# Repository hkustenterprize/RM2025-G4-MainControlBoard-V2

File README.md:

<div align='center'>
    <h1>RM2025 G4主控板V2</h1>
</div>

<div align='center'>
    <h2>RM2024香港科技大学ENTERPRIZE</h2>
</div>

**开源论坛链接：**

**欢迎加入开源交流QQ群：581184202**

## 文件内容

核心板：[点击在线预览](https://kicanvas.org/?github=https%3A%2F%2Fgithub.com%2Fhkustenterprize%2FRM2025-G4-MainControlBoard-V2%2Ftree%2Fmain%2FRM2025_G473_MCB)

扩展板：[点击在线预览](https://kicanvas.org/?github=https%3A%2F%2Fgithub.com%2Fhkustenterprize%2FRM2025-G4-MainControlBoard-V2%2Ftree%2Fmain%2FRM2025_G473_MCB_StdExtend)

~~~
RM2025-G4-MainControlBoard-V2
├── image
├── RM2025_G473_MCB             > 核心板工程文件
├── RM2024_G473_MCB_StdExtend   > 标准扩展板工程文件
├── LICENSE
└── README.md
~~~

开源工程文件设计软件为 **KiCAD 8.0**，可以导入立创EDA

每个工程文件文件夹中的内容:

~~~
xxx
├── ibom             > 焊接工具，由 "Interactive HTML BOM" 插件生成
├── production      > 生产文件，由 "Fabrication Toolkit" 插件生成，将其中的zip文件拖入JLC下单助手即可
├── xxx.kicad_pcb   > PCB
├── xxx.kicad_pro   > 主工程，通过双击这个启动KiCAD
└── xxx.kicad_sch   > 原理图
~~~

## 重要参数

主控板分为核心板（下板）和扩展板（上板），两板之间使用80pin BTB接口连接，尺寸上保持为与C板一致的 60x40mm；核心板包含所有核心芯片，扩展板用于引出接口或进行其他功能的扩展。

- MCU: STM32G473VET6
- IMU: ICM-42688P
- TTL: CH343P *2 
- FDCAN *3
- RS485 (硬件流控) *1
- FLASH: W25N01GVZEIG

## 主要变动

较比上代开源（[RM2024 G4主控板开源](https://github.com/hkustenterprize/RM2024-MainControlBoard)），2025赛季的G4主控板根据需求做出了一些变动和优化，主要变化如下：

- 核心板重新 layout，将 QSPI FLASH 的走线进行了等长
- 移除磁力计，移除 CH343P 的流控引脚连接
- 在核心板上增加两个 GPIO 接口
- 将核心板的 MCU 供电由 Buck 改为 LDO
- 扩展板重新 layout，增加了专用于舵轮分电板的 7pin 接口
- 扩展板增加四个 WS2812 LED用于指示状态，将蜂鸣器移至核心板上

## 电源网络

## 外设引脚分配

| <u>CAN</u> (SIT1042T/3) | CAN_TX | CAN_RX |
| ---- | ---- | ---- |
| **CAN1**   | PD1   | PD0   |
| **CAN2**   | PB6   | PB5  |
| **CAN3**   | PB4   | PB3   |

| <u>RS485</u> (SN75176AD) | TX <sup>1</sup> | RX <sup>1</sup> | DE <sup>2</sup>|
| ---- | ---- | ---- |---- |
| **RS485 (UART4)**   | PC10   | PC11  | PA15 |

1. 不使用RS485功能时 UART4 可作为 独立UART 使用。
2. 不使用RS485功能时 **DE引脚** 需要配置为 **高电平**，需要确保 **RS485接口** 没有连接。

| <u>TTL</u> (CH343P) | TX | RX |
| ---- | ---- | ---- |
| **TTL1 (UART2A)**   | PA2  | PA3  |
| **TTL2 (UART3A)**   | PD8  | PD9  |

- 两个TTL芯片均连有状态指示灯，在接口两侧。
- CH343P 接入USB线 (VBUS有供电) 后自动使能。

| <u>IMU</u> (ICM-42688P) | SCLK | MISO | MOSI | CS | DRDY |
| ---- | ---- | ---- | ---- | ---- | ---- |
| **IMU (SPI2)**   | PB13  | PB14  | PB15 | PB12 | PB10 |

- **IMU加热**开关由 **PA4** 引脚控制，可以使用 **TIM3_CH2** 或 **GPIO SET/RESET**。
- IMU朝向已在板背面标明

| <u>DR16/i10B</u> | RX <sup>1 2</sup> |
| ---- | ---- |
| **RX1 (UART1C)**   | PA10 |
| **RX2 (UART3C)**   | PB11 |

1. 两个引脚硬件上连接在一起，可使用任意一个引脚 (对应的串口) 读取接受机数据。
2. 使用一个引脚时，**另外一个引脚一定要悬空**。

| <u>FLASH</u> (W25N01GVZEIG) | CS | CLK | IO0 | IO1 | IO2 | IO3 |
| ---- | ---- | ---- | ---- | ---- | ---- | ---- |
| **FLASH (QSPI1)**   | PE11  | PE10  | PB1 | PE13 | PE14 | PA6 |

| <u>其他外设</u>  | Pin |
| ---- | ---- |
| **VIN 24V ADC**   | PA8  |
| **5V ADC**   | PA9  |
| **Buzzer**   | PE3  |
| **LED**   | PC13  |
| **Button**   | PC15  |

## 串口分配

|       | TX | RX | DE | 功能 |
| ---- | ---- | ---- | ---- | ---- |
| **UART1A**   | PC4  | PC5  |-      | 裁判系统/图传 |
| **UART1B**   | PE0  | PE1  |- | 通用串口  |
| **UART1C**   | -  | PA10  |-  | 接收机  |
| **UART2A**   | PA2  | PA3  |-  | MiniPC1 TTL |
| **UART2B**   | PD5  | PD6  |-  | 通用串口  |
| **UART3A**   | PD8  | PD9  |-  | MiniPC2 TTL |
| **UART3B**   | PB9  | PE15  |-  | 通用串口  |
| **UART3C**   | -  | PB11  |-  | 接收机  |
| **UART4**   | PC10  | PC11  | PA15 | RS485/通用串口<sup>1</sup>  |
| **UART5**   | PC12  | PD2  |-  | 裁判系统/图传  |

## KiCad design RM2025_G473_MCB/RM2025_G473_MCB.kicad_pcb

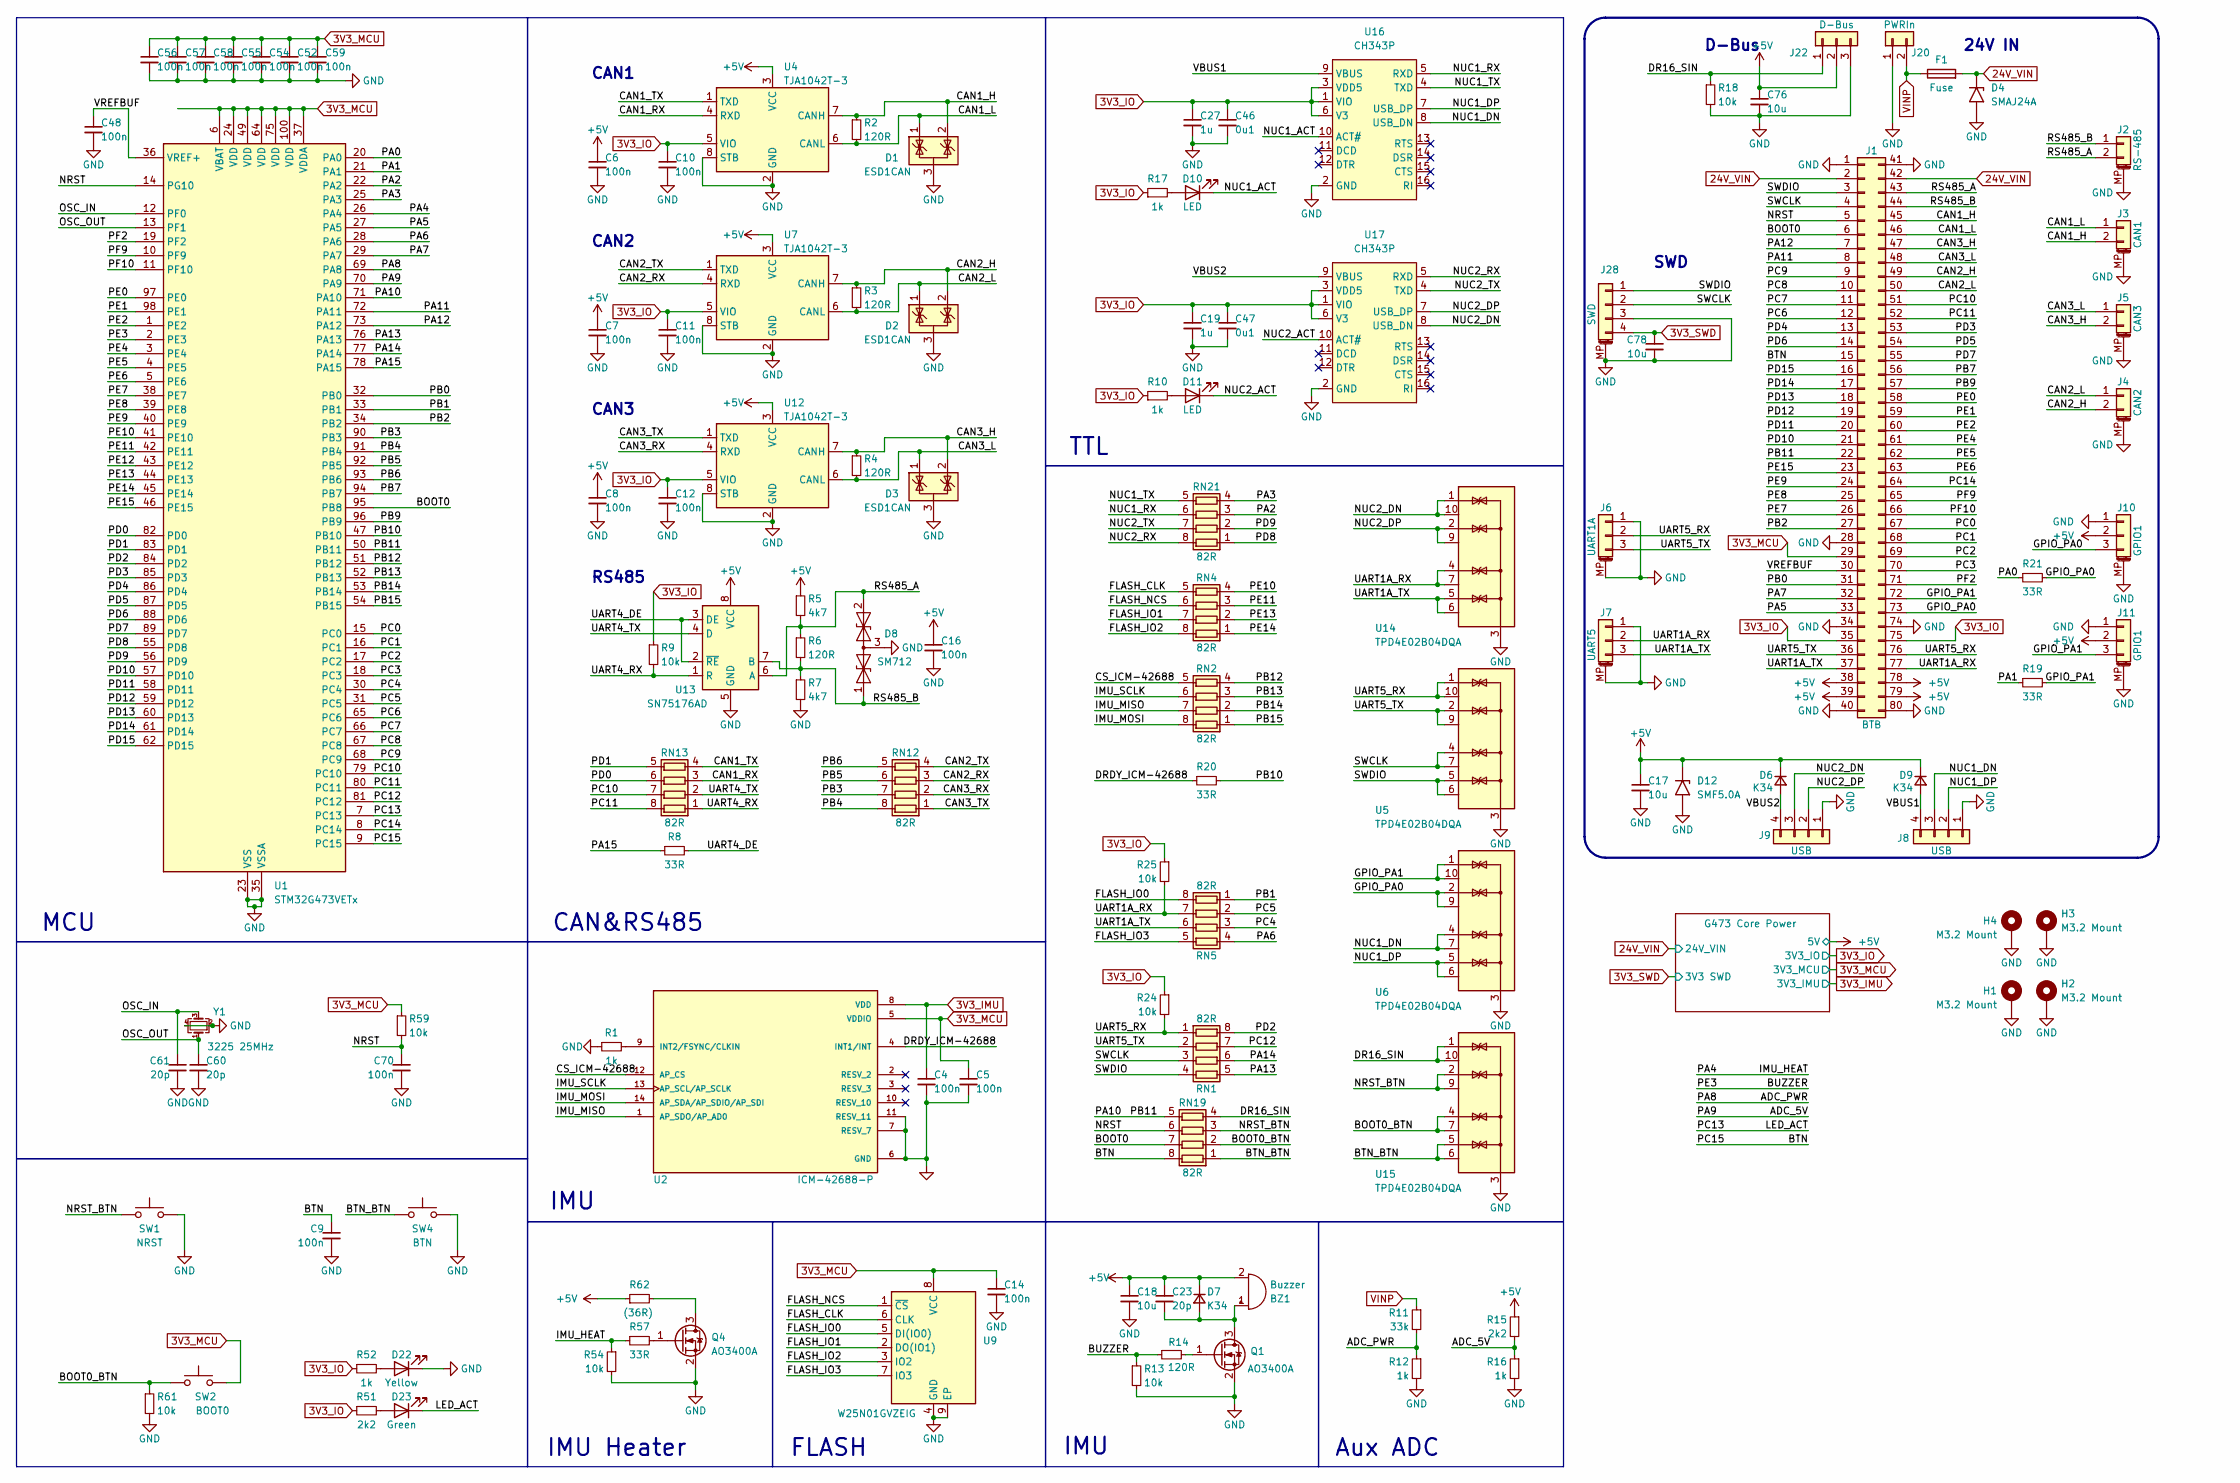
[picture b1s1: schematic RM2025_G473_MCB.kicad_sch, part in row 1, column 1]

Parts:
BZ1: Buzzer; MLT-9032
C4, C5, C6, C7, C8, C9, C10, C11, C12, C14, C16, C48, C52, C54, C55, C56, C57, C58, C59, C70: 100n; C_0603_1608Metric
C17, C18, C76, C78: 10u; C_0603_1608Metric
C19, C27: 1u; C_0603_1608Metric
C23, C60, C61: 20p; C_0603_1608Metric
C46, C47: 0u1; C_0603_1608Metric
D1, D2, D3: ESD1CAN; SOT-23
D4: SMAJ24A; D_SMA
D6, D7, D9: K34; D_SMF
D8: SM712; SOT-23
D10, D11: LED; LED_0603_1608Metric
D12: SMF5.0A; D_SMF
D22: Yellow; LED_0603_1608Metric
D23: Green; LED_0603_1608Metric
F1: Fuse; Fuse_1206_3216Metric
H1, H2, H3, H4: M3.2 Mount; MountingHole_3.2mm_M3_DIN965_Pad
J1: BTB; BTB_P0.8mm_2x40pin_F
J2: RS-485; JST_GH_SM02B-GHS-TB_1x02-1MP_P1.25mm_Horizontal
J3: CAN1; JST_GH_SM02B-GHS-TB_1x02-1MP_P1.25mm_Horizontal
J4: CAN2; JST_GH_SM02B-GHS-TB_1x02-1MP_P1.25mm_Horizontal
J5: CAN3; JST_GH_SM02B-GHS-TB_1x02-1MP_P1.25mm_Horizontal
J6: UART1A; JST_GH_SM03B-GHS-TB_1x03-1MP_P1.25mm_Horizontal
J7: UART5; JST_GH_SM03B-GHS-TB_1x03-1MP_P1.25mm_Horizontal
J8, J9: USB; JST_PH_B4B-PH-K_1x04_P2.00mm_Vertical
J10, J11: GPIO1; JST_GH_SM03B-GHS-TB_1x03-1MP_P1.25mm_Horizontal
J20: PWRIn; AMASS_XT30U-M_1x02_P5.0mm_Vertical
J22: D-Bus; PinHeader_1x03_P2.54mm_Vertical
J28: SWD; Molex_PicoBlade_53261-0471_1x04-1MP_P1.25mm_Horizontal
Q1, Q4: AO3400A; SOT-23
R1, R10, R12, R16, R17, R52: 1k; R_0603_1608Metric
R2, R3, R4, R6, R14: 120R; R_0603_1608Metric
R5, R7: 4k7; R_0603_1608Metric
R8, R19, R20, R21, R57: 33R; R_0603_1608Metric
R9, R13, R18, R24, R25, R54, R59, R61: 10k; R_0603_1608Metric
R11: 33k; R_0603_1608Metric
R15, R51: 2k2; R_0603_1608Metric
R62: (36R); R_1206_3216Metric
RN1, RN2, RN4, RN5, RN12, RN13, RN19, RN21: 82R; R_Array_Concave_4x0603
SW1: NRST; Button_Side
SW2: BOOT0; Button_Side
SW4: BTN; Button_Side
U1: STM32G473VETx; LQFP-100_14x14mm_P0.5mm
U2: ICM-42688-P; PQFN50P300X250X97-14N; PARTREV 1.2
U4, U7, U12: TJA1042T-3; SOIC-8_3.9x4.9mm_P1.27mm
U5, U6, U14, U15: TPD4E02B04DQA; USON-10_2.5x1.0mm_P0.5mm_Mod
U9: W25N01GVZEIG; WSON-8_FLASH
U13: SN75176AD; SOIC-8_3.9x4.9mm_P1.27mm
U16, U17: CH343P; TQFN-16-1EP_3x3mm_P0.5mm_EP1.6x1.6mm
Y1: 3225 25MHz; Crystal_SMD_3225-4Pin_3.2x2.5mm

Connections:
3V3_IMU: C4.1, U2.8 (VDD); also elsewhere on the board
3V3_IO: C10.1, C11.1, C12.1, C19.1, C27.1, C46.1, C47.1, J1.35, J1.75, R9.1, R10.1, R17.1, R24.1, R25.1, R51.1, R52.1, U4.5 (VIO), U7.5 (VIO), U12.5 (VIO), U16.1 (VIO), U16.3 (VDD5), U16.6 (V3), U17.1 (VIO), U17.3 (VDD5), U17.6 (V3); also elsewhere on the board
3V3_MCU: C5.1, C14.1, C52.1, C54.1, C55.1, C56.1, C57.1, C58.1, C59.1, J1.29, R59.1, SW2.2, U1.6 (VBAT), U1.24 (VDD), U1.37 (VDDA), U1.49 (VDD), U1.64 (VDD), U1.75 (VDD), U1.100 (VDD), U2.5 (VDDIO), U9.8 (VCC); also elsewhere on the board
3V3_SWD: C78.1, J28.4; also elsewhere on the board
24V_VIN: D4.1 (A1), F1.2, J1.2, J1.42; also elsewhere on the board
+5V: BZ1.2 (+), C6.1, C7.1, C8.1, C16.1, C17.1, C18.1, C23.1, C76.1, D6.1 (K), D7.1 (K), D9.1 (K), D12.1 (A1), J1.38, J1.39, J1.78, J1.79, J10.2, J11.2, J22.2, R5.1, R15.1, R62.1, U4.3 (VCC), U7.3 (VCC), U12.3 (VCC), U13.8 (VCC); also elsewhere on the board
/ADC_5V: R15.2, R16.1, U1.70 (PA9)
/ADC_PWR: R11.2, R12.1, U1.69 (PA8)
/BOOT0: J1.6, RN19.7 (R2.2), U1.95 (PB8)
/BOOT0_BTN: R61.1, RN19.2 (R2.1), SW2.1, U15.4 (IO3), U15.7 (NC)
/BTN: C9.1, J1.15, RN19.8 (R1.2), U1.9 (PC15)
/BTN_BTN: RN19.1 (R1.1), SW4.1, U15.5 (IO4), U15.6 (NC)
/BUZZER: R13.1, R14.1, U1.2 (PE3)
/CAN1_H: D1.2 (K), J1.45, J3.2, R2.1, U4.7 (CANH)
/CAN1_L: D1.1 (K), J1.46, J3.1, R2.2, U4.6 (CANL)
/CAN1_RX: RN13.3 (R3.1), U4.4 (RXD)
/CAN1_TX: RN13.4 (R4.1), U4.1 (TXD)
/CAN2_H: D2.2 (K), J1.49, J4.2, R3.1, U7.7 (CANH)
/CAN2_L: D2.1 (K), J1.50, J4.1, R3.2, U7.6 (CANL)
/CAN2_RX: RN12.3 (R3.1), U7.4 (RXD)
/CAN2_TX: RN12.4 (R4.1), U7.1 (TXD)
/CAN3_H: D3.2 (K), J1.47, J5.2, R4.1, U12.7 (CANH)
/CAN3_L: D3.1 (K), J1.48, J5.1, R4.2, U12.6 (CANL)
/CAN3_RX: RN12.2 (R2.1), U12.4 (RXD)
/CAN3_TX: RN12.1 (R1.1), U12.1 (TXD)
/CS_ICM-42688: RN2.5 (R4.2), U2.12 (AP_CS)
/DR16_SIN: J22.1, R18.1, RN19.4 (R4.1), U15.1 (IO1), U15.10 (NC)
/DRDY_ICM-42688: R20.1, U2.4 (INT1/INT)
/FLASH_CLK: RN4.5 (R4.2), U9.6 (CLK)
/FLASH_IO0: RN5.8 (R1.2), U9.5 (DI(IO0))
/FLASH_IO1: RN4.7 (R2.2), U9.2 (DO(IO1))
/FLASH_IO2: RN4.8 (R1.2), U9.3 (IO2)
/FLASH_IO3: RN5.5 (R4.2), U9.7 (IO3)
/FLASH_NCS: RN4.6 (R3.2), U9.1 (~CS)
/GPIO_PA0: J1.73, J10.3, R21.2, U6.2 (IO2), U6.9 (NC)
/GPIO_PA1: J1.72, J11.3, R19.2, U6.1 (IO1), U6.10 (NC)
/IMU_HEAT: R54.1, R57.1, U1.26 (PA4)
/IMU_MISO: RN2.7 (R2.2), U2.1 (AP_SDO/AP_AD0)
/IMU_MOSI: RN2.8 (R1.2), U2.14 (AP_SDA/AP_SDIO/AP_SDI)
/IMU_SCLK: RN2.6 (R3.2), U2.13 (AP_SCL/AP_SCLK)
/LED_ACT: D23.1 (K), U1.7 (PC13)
/NRST: C70.1, J1.5, R59.2, RN19.6 (R3.2), U1.14 (PG10)
/NRST_BTN: RN19.3 (R3.1), SW1.1, U15.2 (IO2), U15.9 (NC)
/NUC1_ACT: D10.1 (K), U16.10 (ACT#)
/NUC1_DN: J8.3, U6.4 (IO3), U6.7 (NC), U16.8 (USB_DN)
/NUC1_DP: J8.2, U6.5 (IO4), U6.6 (NC), U16.7 (USB_DP)
/NUC1_RX: RN21.6 (R3.2), U16.5 (RXD)
/NUC1_TX: RN21.5 (R4.2), U16.4 (TXD)
/NUC2_ACT: D11.1 (K), U17.10 (ACT#)
/NUC2_DN: J9.3, U14.1 (IO1), U14.10 (NC), U17.8 (USB_DN)
/NUC2_DP: J9.2, U14.2 (IO2), U14.9 (NC), U17.7 (USB_DP)
/NUC2_RX: RN21.8 (R1.2), U17.5 (RXD)
/NUC2_TX: RN21.7 (R2.2), U17.4 (TXD)
/OSC_IN: C61.1, U1.12 (PF0), Y1.3
/OSC_OUT: C60.1, U1.13 (PF1), Y1.1
/PA0: R21.1, U1.20 (PA0)
/PA1: R19.1, U1.21 (PA1)
/PA2: RN21.3 (R3.1), U1.22 (PA2)
/PA3: RN21.4 (R4.1), U1.25 (PA3)
/PA5: J1.33, U1.27 (PA5)
/PA6: RN5.4 (R4.1), U1.28 (PA6)
/PA7: J1.32, U1.29 (PA7)
/PA10: J1.22, RN19.5 (R4.2), U1.50 (PB11), U1.71 (PA10)
/PA11: J1.8, U1.72 (PA11)
/PA12: J1.7, U1.73 (PA12)
/PA13: RN1.5 (R4.2), U1.76 (PA13)
/PA14: RN1.6 (R3.2), U1.77 (PA14)
/PA15: R8.1, U1.78 (PA15)
/PB0: J1.31, U1.32 (PB0)
/PB1: RN5.1 (R1.1), U1.33 (PB1)
/PB2: J1.27, U1.34 (PB2)
/PB3: RN12.7 (R2.2), U1.90 (PB3)
/PB4: RN12.8 (R1.2), U1.91 (PB4)
/PB5: RN12.6 (R3.2), U1.92 (PB5)
/PB6: RN12.5 (R4.2), U1.93 (PB6)
/PB7: J1.56, U1.94 (PB7)
/PB9: J1.57, U1.96 (PB9)
/PB10: R20.2, U1.47 (PB10)
/PB12: RN2.4 (R4.1), U1.51 (PB12)
/PB13: RN2.3 (R3.1), U1.52 (PB13)
/PB14: RN2.2 (R2.1), U1.53 (PB14)
/PB15: RN2.1 (R1.1), U1.54 (PB15)
/PC0: J1.67, U1.15 (PC0)
/PC1: J1.68, U1.16 (PC1)
/PC2: J1.69, U1.17 (PC2)
/PC3: J1.70, U1.18 (PC3)
/PC4: RN5.3 (R3.1), U1.30 (PC4)
/PC5: RN5.2 (R2.1), U1.31 (PC5)
/PC6: J1.12, U1.65 (PC6)
/PC7: J1.11, U1.66 (PC7)
/PC8: J1.10, U1.67 (PC8)
/PC9: J1.9, U1.68 (PC9)
/PC10: J1.51, RN13.7 (R2.2), U1.79 (PC10)
/PC11: J1.52, RN13.8 (R1.2), U1.80 (PC11)
/PC12: RN1.7 (R2.2), U1.81 (PC12)
/PC14: J1.64, U1.8 (PC14)
/PD0: RN13.6 (R3.2), U1.82 (PD0)
/PD1: RN13.5 (R4.2), U1.83 (PD1)
/PD2: RN1.8 (R1.2), U1.84 (PD2)
/PD3: J1.53, U1.85 (PD3)
/PD4: J1.13, U1.86 (PD4)
/PD5: J1.54, U1.87 (PD5)
/PD6: J1.14, U1.88 (PD6)
/PD7: J1.55, U1.89 (PD7)
/PD8: RN21.1 (R1.1), U1.55 (PD8)
/PD9: RN21.2 (R2.1), U1.56 (PD9)
/PD10: J1.21, U1.57 (PD10)
/PD11: J1.20, U1.58 (PD11)
/PD12: J1.19, U1.59 (PD12)
/PD13: J1.18, U1.60 (PD13)
/PD14: J1.17, U1.61 (PD14)
/PD15: J1.16, U1.62 (PD15)
/PE0: J1.58, U1.97 (PE0)
/PE1: J1.59, U1.98 (PE1)
/PE2: J1.60, U1.1 (PE2)
/PE4: J1.61, U1.3 (PE4)
/PE5: J1.62, U1.4 (PE5)
/PE6: J1.63, U1.5 (PE6)
/PE7: J1.26, U1.38 (PE7)
/PE8: J1.25, U1.39 (PE8)
/PE9: J1.24, U1.40 (PE9)
/PE10: RN4.4 (R4.1), U1.41 (PE10)
/PE11: RN4.3 (R3.1), U1.42 (PE11)
/PE12: U1.43 (PE12)
/PE13: RN4.2 (R2.1), U1.44 (PE13)
/PE14: RN4.1 (R1.1), U1.45 (PE14)
/PE15: J1.23, U1.46 (PE15)
/PF2: J1.71, U1.19 (PF2)
/PF9: J1.65, U1.10 (PF9)
/PF10: J1.66, U1.11 (PF10)
/RS485_A: D8.2 (A2), J1.43, J2.2, R5.2, R6.1, U13.6 (A)
/RS485_B: D8.1 (A1), J1.44, J2.1, R6.2, R7.1, U13.7 (B)
/SWCLK: J1.4, J28.2, RN1.3 (R3.1), U5.4 (IO3), U5.7 (NC)
/SWDIO: J1.3, J28.1, RN1.4 (R4.1), U5.5 (IO4), U5.6 (NC)
/UART1A_RX: J1.77, J7.2, R25.2, RN5.7 (R2.2), U14.4 (IO3), U14.7 (NC)
/UART1A_TX: J1.37, J7.3, RN5.6 (R3.2), U14.5 (IO4), U14.6 (NC)
/UART4_DE: R8.2, U13.2 (~RE), U13.3 (DE)
/UART4_RX: R9.2, RN13.1 (R1.1), U13.1 (R)
/UART4_TX: RN13.2 (R2.1), U13.4 (D)
/UART5_RX: J1.76, J6.2, R24.2, RN1.1 (R1.1), U5.1 (IO1), U5.10 (NC)
/UART5_TX: J1.36, J6.3, RN1.2 (R2.1), U5.2 (IO2), U5.9 (NC)
/VBUS1: D9.2 (A), J8.4, U16.9 (VBUS)
/VBUS2: D6.2 (A), J9.4, U17.9 (VBUS)
/VREFBUF: C48.1, J1.30, U1.36 (VREF+)
GND: C4.2, C5.2, C6.2, C7.2, C8.2, C9.2, C10.2, C11.2, C12.2, C14.2, C16.2, C17.2, C18.2, C19.2, C27.2, C46.2, C47.2, C48.2, C52.2, C54.2, C55.2, C56.2, C57.2, C58.2, C59.2, C60.2, C61.2, C70.2, C76.2, C78.2, D1.3 (A), D2.3 (A), D3.3 (A), D4.2 (A2), D8.3 (common), D12.2 (A2), D22.1 (K), H1.1, H2.1, H3.1, H4.1, J1.1, J1.28, J1.34, J1.40, J1.41, J1.74, J1.80, J2.MP (MountPin), J3.MP (MountPin), J4.MP (MountPin), J5.MP (MountPin), J6.1, J6.MP (MountPin), J7.1, J7.MP (MountPin), J8.1, J9.1, J10.1, J10.MP (MountPin), J11.1, J11.MP (MountPin), J20.1, J22.3, J28.3, J28.MP (MountPin), Q1.2 (S), Q4.2 (S), R1.1, R7.2, R12.2, R13.2, R16.2, R18.2, R54.2, R61.2, SW1.2, SW4.2, U1.23 (VSS), U1.35 (VSSA), U1.48 (VSS), U1.63 (VSS), U1.74 (VSS), U1.99 (VSS), U2.6 (GND), U2.7 (RESV_7), U2.11 (RESV_11), U4.2 (GND), U4.8 (STB), U5.3 (G), U5.8 (G), U6.3 (G), U6.8 (G), U7.2 (GND), U7.8 (STB), U9.4 (GND), U9.9 (EP), U12.2 (GND), U12.8 (STB), U13.5 (GND), U14.3 (G), U14.8 (G), U15.3 (G), U15.8 (G), U16.2 (GND), U16.17 (GND), U17.2 (GND), U17.17 (GND), Y1.2, Y1.4; also elsewhere on the board
unnamed: BZ1.1 (-), C23.2, D7.2 (A), Q1.3 (D)
unnamed: D10.2 (A), R17.2
unnamed: D11.2 (A), R10.2
unnamed: D22.2 (A), R52.2
unnamed: D23.2 (A), R51.2
unnamed: Q1.1 (G), R14.2
unnamed: Q4.3 (D), R62.2
unnamed: Q4.1 (G), R57.2
unnamed: R1.2, U2.9 (INT2/FSYNC/CLKIN)
VINP: F1.1, J20.2, R11.1

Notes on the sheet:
CAN1
24V IN
CAN&RS485
IMU
CAN3
RS485
FLASH
SWD
TTL
Aux ADC
MCU
IMU Heater
D-Bus
CAN2

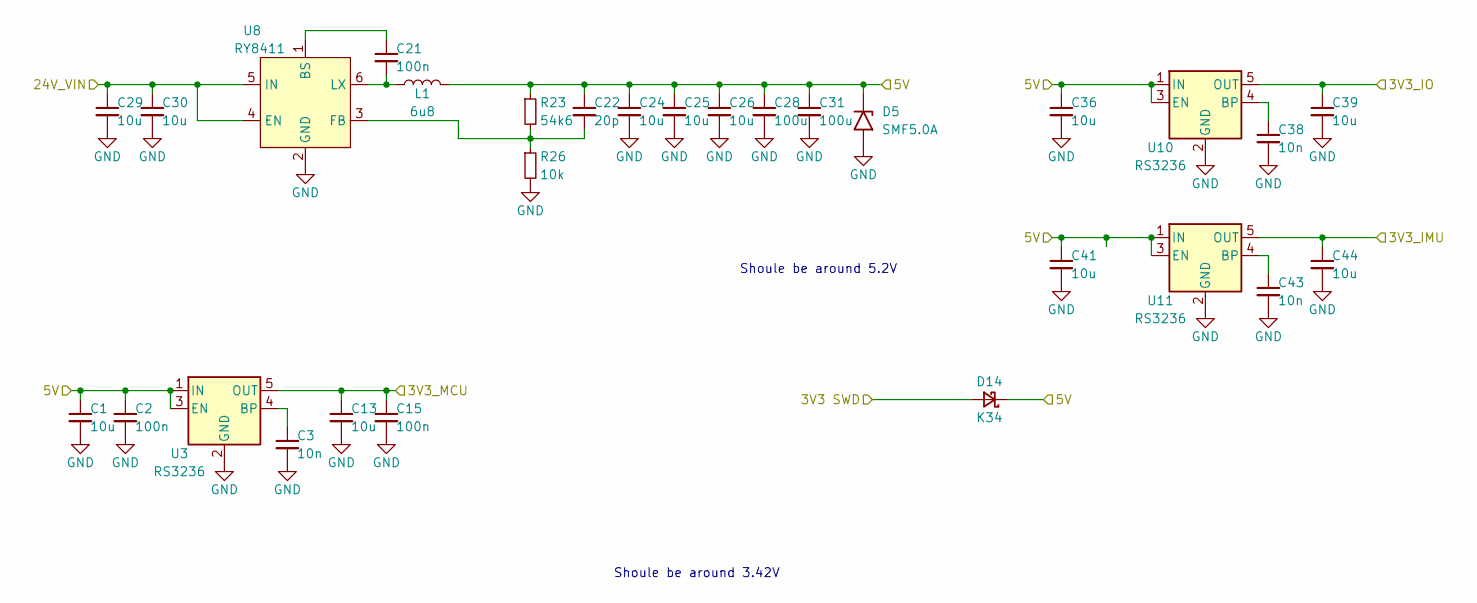
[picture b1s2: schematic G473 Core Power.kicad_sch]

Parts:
C1, C13, C36, C39, C41, C44: 10u; C_0603_1608Metric
C2, C15, C21: 100n; C_0603_1608Metric
C3, C38, C43: 10n; C_0603_1608Metric
C22: 20p; C_0603_1608Metric
C24, C25, C26, C29, C30: 10u; C_1206_3216Metric
C28, C31: 100u; C_1206_3216Metric
D5: SMF5.0A; D_SMF
D14: K34; D_SMF
L1: 6u8; L_Sunlord_MWSA0402S
R23: 54k6; R_0603_1608Metric
R26: 10k; R_0603_1608Metric
U3, U10, U11: RS3236; SOT-23-5
U8: RY8411; SOT-23-6

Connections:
3V3_IMU: C44.1, U11.5 (OUT); also elsewhere on the board
3V3_IO: C39.1, U10.5 (OUT); also elsewhere on the board
3V3_MCU: C13.1, C15.1, U3.5 (OUT); also elsewhere on the board
3V3_SWD: D14.2 (A); also elsewhere on the board
24V_VIN: C29.1, C30.1, U8.4 (EN), U8.5 (IN); also elsewhere on the board
+5V: C1.1, C2.1, C22.1, C24.1, C25.1, C26.1, C28.1, C31.1, C36.1, C41.1, D5.1 (A1), D14.1 (K), L1.2, R23.1, U3.1 (IN), U3.3 (EN), U10.1 (IN), U10.3 (EN), U11.1 (IN), U11.3 (EN); also elsewhere on the board
GND: C1.2, C2.2, C3.2, C13.2, C15.2, C24.2, C25.2, C26.2, C28.2, C29.2, C30.2, C31.2, C36.2, C38.2, C39.2, C41.2, C43.2, C44.2, D5.2 (A2), R26.2, U3.2 (GND), U8.2 (GND), U10.2 (GND), U11.2 (GND); also elsewhere on the board
unnamed: C3.1, U3.4 (BP)
unnamed: C21.1, U8.1 (BS)
unnamed: C22.2, R23.2, R26.1, U8.3 (FB)
unnamed: C21.2, L1.1, U8.6 (LX)
unnamed: C38.1, U10.4 (BP)
unnamed: C43.1, U11.4 (BP)

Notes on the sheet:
Shoule be around 5.2V
Shoule be around 3.42V

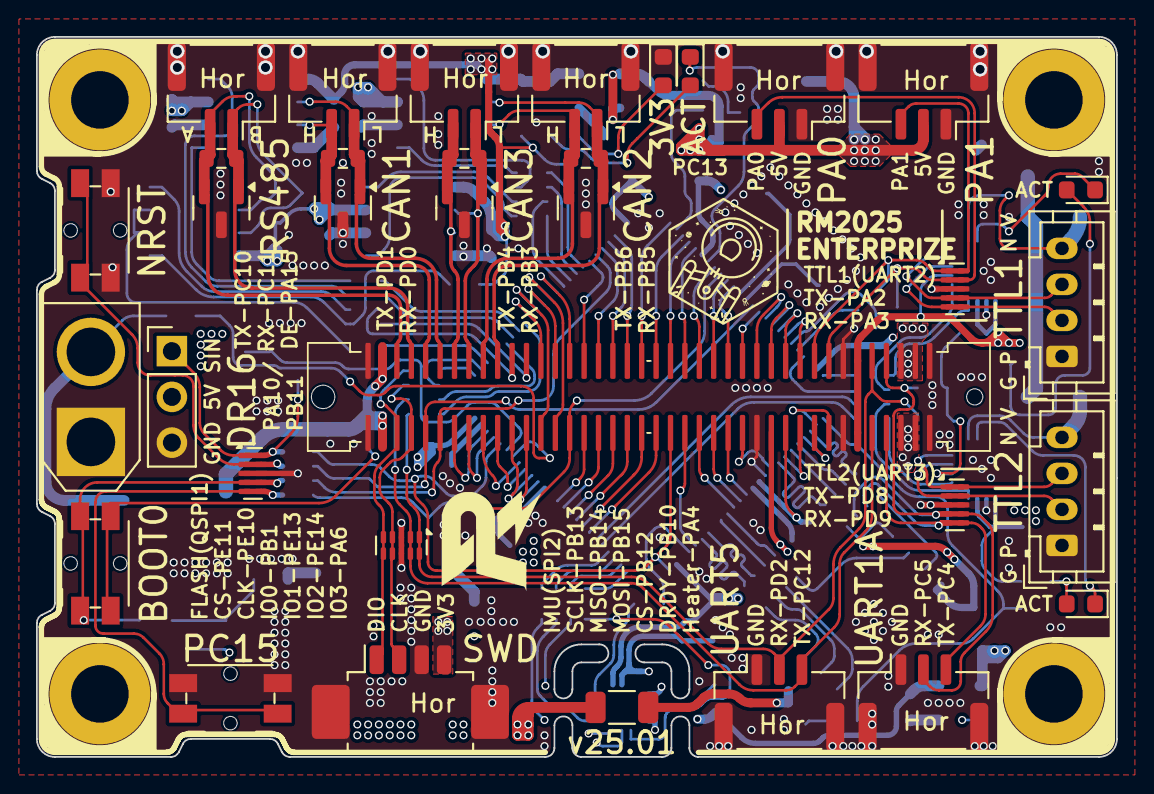
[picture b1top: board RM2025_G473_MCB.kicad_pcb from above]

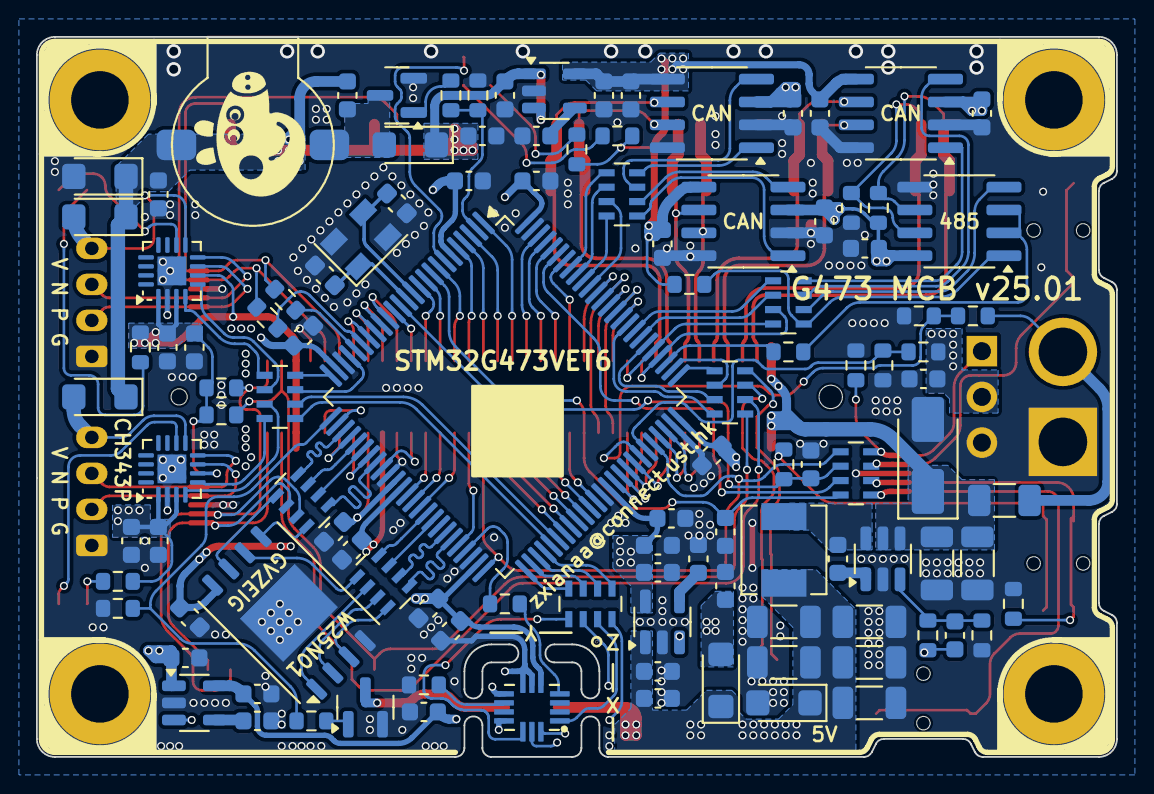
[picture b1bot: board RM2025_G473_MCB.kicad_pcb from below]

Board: 4 copper layers, 60.0 x 40.0 mm, 150 parts (112 on the bottom side), 160 nets.

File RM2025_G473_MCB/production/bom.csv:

Designator,Footprint,Quantity,Value,LCSC Part #
BZ1,MLT-9032,1,Buzzer,
"C1, C13, C17, C18, C36, C39, C41, C44, C76, C78",0603,10,10u,
"C10, C11, C12, C14, C15, C16, C2, C21, C4, C48, C5, C52, C54, C55, C56, C57, C58, C59, C6, C7, C70, C8, C9",0603,23,100n,
"C19, C27",0603,2,1u,
"C22, C23, C60, C61",0603,4,20p,
"C24, C25, C26, C29, C30",1206,5,10u,
"C28, C31",1206,2,100u,
"C3, C38, C43",0603,3,10n,
"C46, C47",0603,2,0u1,
"D1, D2, D3",SOT-23,3,ESD1CAN,
"D10, D11",0603,2,LED,
"D12, D5",D_SMF,2,SMF5.0A,
"D14, D6, D7, D9",D_SMF,4,K34,
D22,0603,1,Yellow,
D23,0603,1,Green,
D4,D_SMA,1,SMAJ24A,
D8,SOT-23,1,SM712,
F1,1206,1,Fuse,
J1,BTB_P0.8mm_2x40pin_F,1,BTB,
"J10, J11",JST_GH_SM03B-GHS-TB_1x03-1MP_P1.25mm_Horizontal,2,GPIO1,
J2,JST_GH_SM02B-GHS-TB_1x02-1MP_P1.25mm_Horizontal,1,RS-485,
J20,AMASS_XT30U-M_1x02_P5.0mm_Vertical,1,PWRIn,
J22,PinHeader_1x03_P2.54mm_Vertical,1,D-Bus,
J28,Molex_PicoBlade_53261-0471_1x04-1MP_P1.25mm_Horizontal,1,SWD,
J3,JST_GH_SM02B-GHS-TB_1x02-1MP_P1.25mm_Horizontal,1,CAN1,
J4,JST_GH_SM02B-GHS-TB_1x02-1MP_P1.25mm_Horizontal,1,CAN2,
J5,JST_GH_SM02B-GHS-TB_1x02-1MP_P1.25mm_Horizontal,1,CAN3,
J6,JST_GH_SM03B-GHS-TB_1x03-1MP_P1.25mm_Horizontal,1,UART1A,
J7,JST_GH_SM03B-GHS-TB_1x03-1MP_P1.25mm_Horizontal,1,UART5,
"J8, J9",JST_PH_B4B-PH-K_1x04_P2.00mm_Vertical,2,USB,
L1,L_Sunlord_MWSA0402S,1,6u8,
"Q1, Q4",SOT-23,2,AO3400A,
"R1, R10, R12, R16, R17, R52",0603,6,1k,
R11,0603,1,33k,
"R13, R18, R24, R25, R26, R54, R59, R61, R9",0603,9,10k,
"R14, R2, R3, R4, R6",0603,5,120R,
"R15, R51",0603,2,2k2,
"R19, R20, R21, R57, R8",0603,5,33R,
R23,0603,1,54k6,
"R5, R7",0603,2,4k7,
R62,1206,1,(36R),
"RN1, RN12, RN13, RN19, RN2, RN21, RN4, RN5",R_Array_Concave_4x0603,8,82R,
SW1,Button_Side,1,NRST,
SW2,Button_Side,1,BOOT0,
SW4,Button_Side,1,BTN,
U1,LQFP-100_14x14mm_P0.5mm,1,STM32G473VETx,
"U10, U11, U3",SOT-23-5,3,RS3236,
"U12, U4, U7",SOIC-8_3.9x4.9mm_P1.27mm,3,TJA1042T-3,
U13,SOIC-8_3.9x4.9mm_P1.27mm,1,SN75176AD,
"U14, U15, U5, U6",USON-10_2.5x1.0mm_P0.5mm_Mod,4,TPD4E02B04DQA,
"U16, U17",TQFN-16-1EP_3x3mm_P0.5mm_EP1.6x1.6mm,2,CH343P,
U2,PQFN50P300X250X97-14N,1,ICM-42688-P,
U8,SOT-23-6,1,RY8411,
U9,WSON-8_FLASH,1,W25N01GVZEIG,
Y1,Crystal_SMD_3225-4Pin_3.2x2.5mm,1,3225 25MHz,

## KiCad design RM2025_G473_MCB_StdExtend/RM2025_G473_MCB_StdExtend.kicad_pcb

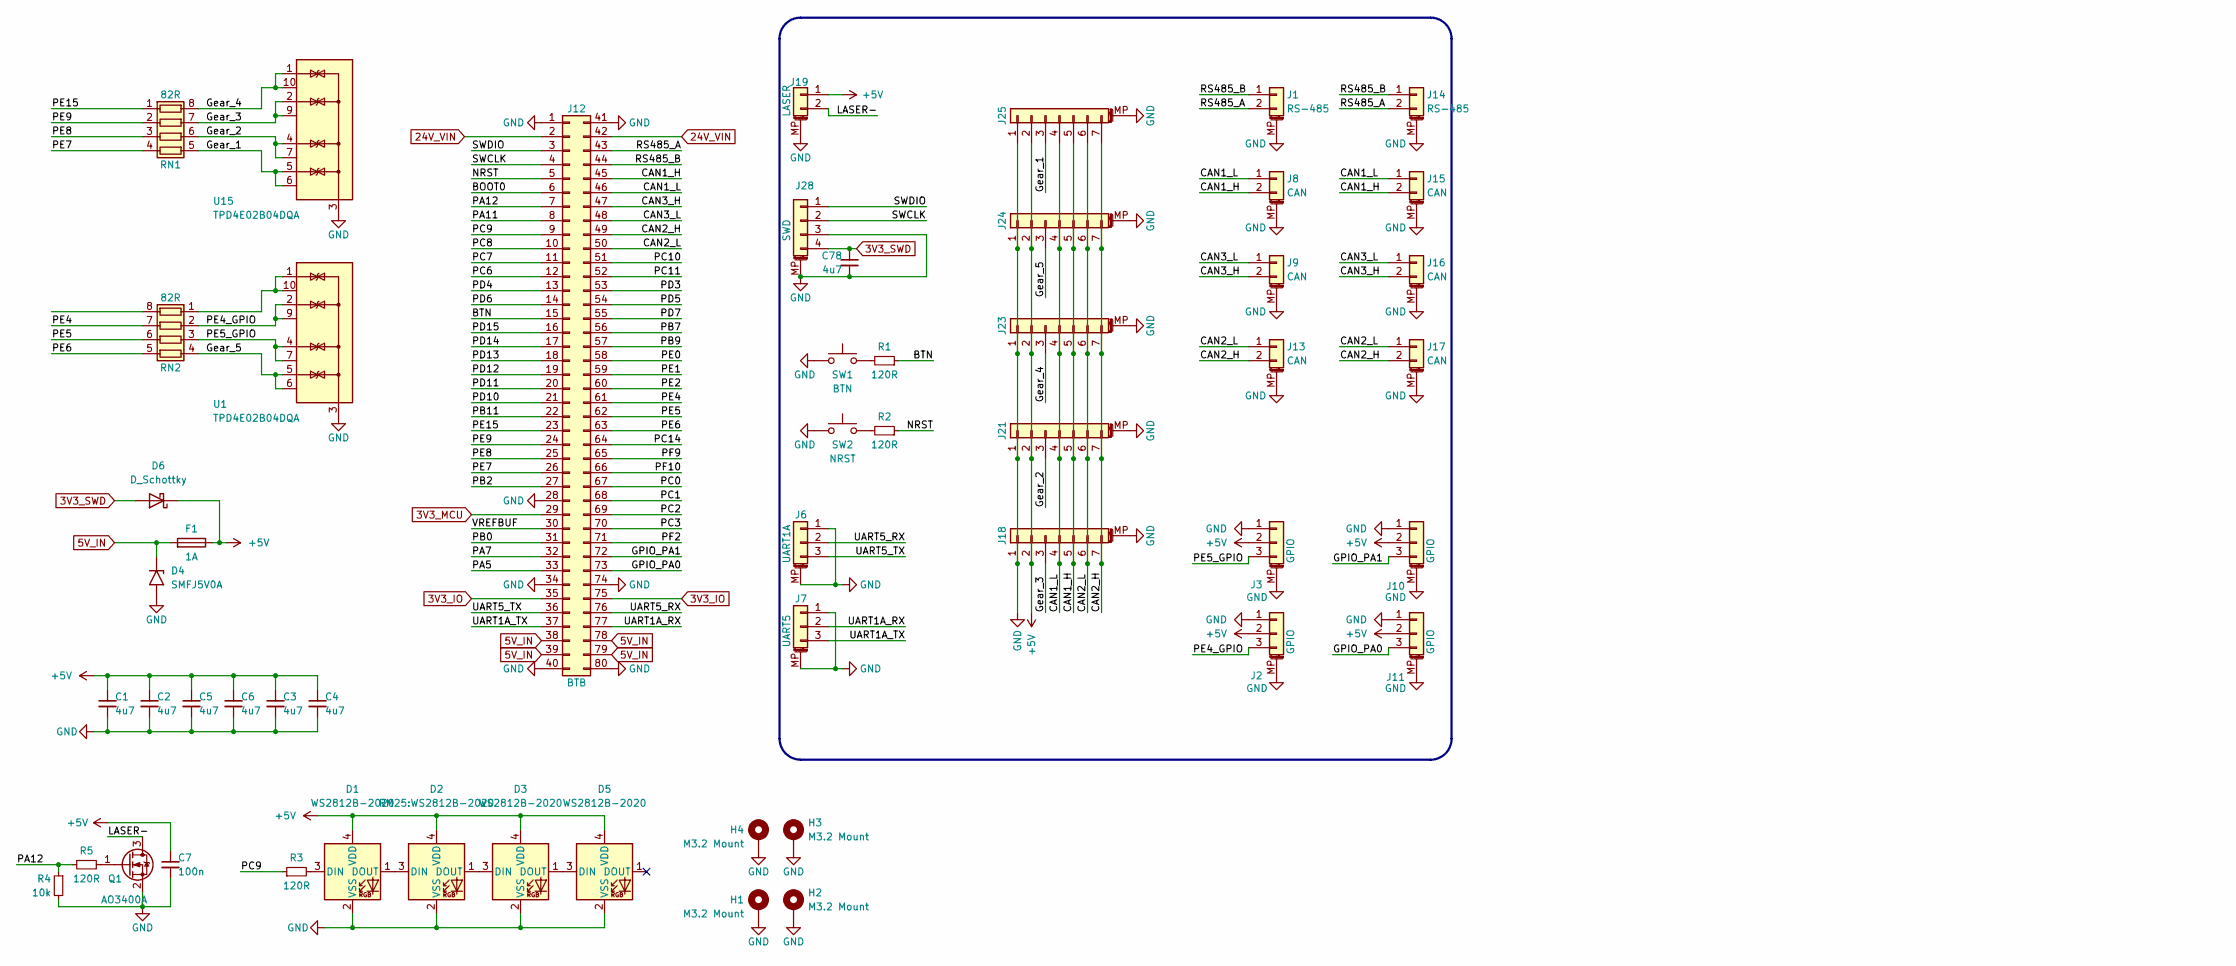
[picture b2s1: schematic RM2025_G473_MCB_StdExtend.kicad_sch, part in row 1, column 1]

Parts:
C1, C2, C3, C4, C5, C6, C78: 4u7; C_0603_1608Metric
C7: 100n; C_0603_1608Metric
D1, D3, D5: WS2812B-2020
D2: RM25:WS2812B-2020; WS2812B-2020
D4: SMFJ5V0A; D_SMF
D6: D_Schottky; D_SMF
F1: 1A; Fuse_1206_3216Metric
H1, H2, H3, H4: M3.2 Mount; MountingHole_3.2mm_M3_DIN965_Pad
J1, J14: RS-485; JST_GH_BM02B-GHS-TBT_1x02-1MP_P1.25mm_Vertical
J2, J3, J10, J11: GPIO; JST_GH_BM03B-GHS-TBT_1x03-1MP_P1.25mm_Vertical
J6: UART1A; JST_GH_BM03B-GHS-TBT_1x03-1MP_P1.25mm_Vertical
J7: UART5; JST_GH_BM03B-GHS-TBT_1x03-1MP_P1.25mm_Vertical
J8, J9, J13, J15, J16, J17: CAN; JST_GH_BM02B-GHS-TBT_1x02-1MP_P1.25mm_Vertical
J12: BTB; BTB_P0.8mm_2x40pin_M
J18, J21, J23, J24, J25: Conn_01x07_MountingPin; JST_GH_BM07B-GHS-TBT_1x07-1MP_P1.25mm_Vertical
J19: LASER; Molex_PicoBlade_53261-0271_1x02-1MP_P1.25mm_Horizontal
J28: SWD; Molex_PicoBlade_53261-0471_1x04-1MP_P1.25mm_Horizontal
Q1: AO3400A; SOT-23
R1, R2, R3, R5: 120R; R_0603_1608Metric
R4: 10k; R_0603_1608Metric
RN1, RN2: 82R; R_Array_Concave_4x0603
SW1: BTN; Button_PTS810
SW2: NRST; Button_PTS810
U1, U15: TPD4E02B04DQA; USON-10_2.5x1.0mm_P0.5mm_Mod

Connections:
3V3_IO: J12.35, J12.75
3V3_MCU: J12.29
3V3_SWD: C78.1, D6.2 (A), J28.4
5V_IN: D4.1 (A1), F1.2, J12.38, J12.39, J12.78, J12.79
24V_VIN: J12.2, J12.42
+5V: C1.1, C2.1, C3.1, C4.1, C5.1, C6.1, C7.1, D1.4 (VDD), D2.4 (VDD), D3.4 (VDD), D5.4 (VDD), D6.1 (K), F1.1, J2.2, J3.2, J10.2, J11.2, J18.2, J19.1, J21.2, J23.2, J24.2, J25.2
/BOOT0: J12.6
/BTN: J12.15, R1.1
/CAN1_H: J8.2, J12.45, J15.2, J18.5, J21.5, J23.5, J24.5, J25.5
/CAN1_L: J8.1, J12.46, J15.1, J18.4, J21.4, J23.4, J24.4, J25.4
/CAN2_H: J12.49, J13.2, J17.2, J18.7, J21.7, J23.7, J24.7, J25.7
/CAN2_L: J12.50, J13.1, J17.1, J18.6, J21.6, J23.6, J24.6, J25.6
/CAN3_H: J9.2, J12.47, J16.2
/CAN3_L: J9.1, J12.48, J16.1
/GPIO_PA0: J11.3, J12.73
/GPIO_PA1: J10.3, J12.72
/Gear_1: J25.3, RN1.5 (R4.2), U15.5 (IO4), U15.6 (NC)
/Gear_2: J21.3, RN1.6 (R3.2), U15.4 (IO3), U15.7 (NC)
/Gear_3: J18.3, RN1.7 (R2.2), U15.2 (IO2), U15.9 (NC)
/Gear_4: J23.3, RN1.8 (R1.2), U15.1 (IO1), U15.10 (NC)
/Gear_5: J24.3, RN2.4 (R4.1), U1.5 (IO4), U1.6 (NC)
/LASER-: J19.2, Q1.3 (D)
/NRST: J12.5, R2.1
/PA5: J12.33
/PA7: J12.32
/PA11: J12.8
/PA12: J12.7, R4.1, R5.1
/PB0: J12.31
/PB2: J12.27
/PB7: J12.56
/PB9: J12.57
/PB11: J12.22
/PC0: J12.67
/PC1: J12.68
/PC2: J12.69
/PC3: J12.70
/PC6: J12.12
/PC7: J12.11
/PC8: J12.10
/PC9: J12.9, R3.1
/PC10: J12.51
/PC11: J12.52
/PC14: J12.64
/PD3: J12.53
/PD4: J12.13
/PD5: J12.54
/PD6: J12.14
/PD7: J12.55
/PD10: J12.21
/PD11: J12.20
/PD12: J12.19
/PD13: J12.18
/PD14: J12.17
/PD15: J12.16
/PE0: J12.58
/PE1: J12.59
/PE2: J12.60
/PE4: J12.61, RN2.7 (R2.2)
/PE4_GPIO: J2.3, RN2.2 (R2.1), U1.2 (IO2), U1.9 (NC)
/PE5: J12.62, RN2.6 (R3.2)
/PE5_GPIO: J3.3, RN2.3 (R3.1), U1.4 (IO3), U1.7 (NC)
/PE6: J12.63, RN2.5 (R4.2)
/PE7: J12.26, RN1.4 (R4.1)
/PE8: J12.25, RN1.3 (R3.1)
/PE9: J12.24, RN1.2 (R2.1)
/PE15: J12.23, RN1.1 (R1.1)
/PF2: J12.71
/PF9: J12.65
/PF10: J12.66
/RS485_A: J1.2, J12.43, J14.2
/RS485_B: J1.1, J12.44, J14.1
/SWCLK: J12.4, J28.2
/SWDIO: J12.3, J28.1
/UART1A_RX: J7.2, J12.77
/UART1A_TX: J7.3, J12.37
/UART5_RX: J6.2, J12.76
/UART5_TX: J6.3, J12.36
/VREFBUF: J12.30
GND: C1.2, C2.2, C3.2, C4.2, C5.2, C6.2, C7.2, C78.2, D1.2 (VSS), D2.2 (VSS), D3.2 (VSS), D4.2 (A2), D5.2 (VSS), H1.1, H2.1, H3.1, H4.1, J1.MP (MountPin), J2.1, J2.MP (MountPin), J3.1, J3.MP (MountPin), J6.1, J6.MP (MountPin), J7.1, J7.MP (MountPin), J8.MP (MountPin), J9.MP (MountPin), J10.1, J10.MP (MountPin), J11.1, J11.MP (MountPin), J12.1, J12.28, J12.34, J12.40, J12.41, J12.74, J12.80, J13.MP (MountPin), J14.MP (MountPin), J15.MP (MountPin), J16.MP (MountPin), J17.MP (MountPin), J18.1, J18.MP (MountPin), J19.MP (MountPin), J21.1, J21.MP (MountPin), J23.1, J23.MP (MountPin), J24.1, J24.MP (MountPin), J25.1, J25.MP (MountPin), J28.3, J28.MP (MountPin), Q1.2 (S), R4.2, SW1.2, SW2.2, U1.3 (G), U1.8 (G), U15.3 (G), U15.8 (G)
unnamed: D1.3 (DIN), R3.2
unnamed: D1.1 (DOUT), D2.3 (DIN)
unnamed: D2.1 (DOUT), D3.3 (DIN)
unnamed: D3.1 (DOUT), D5.3 (DIN)
unnamed: Q1.1 (G), R5.2
unnamed: R1.2, SW1.1
unnamed: R2.2, SW2.1
unnamed: RN2.1 (R1.1), U1.1 (IO1), U1.10 (NC)

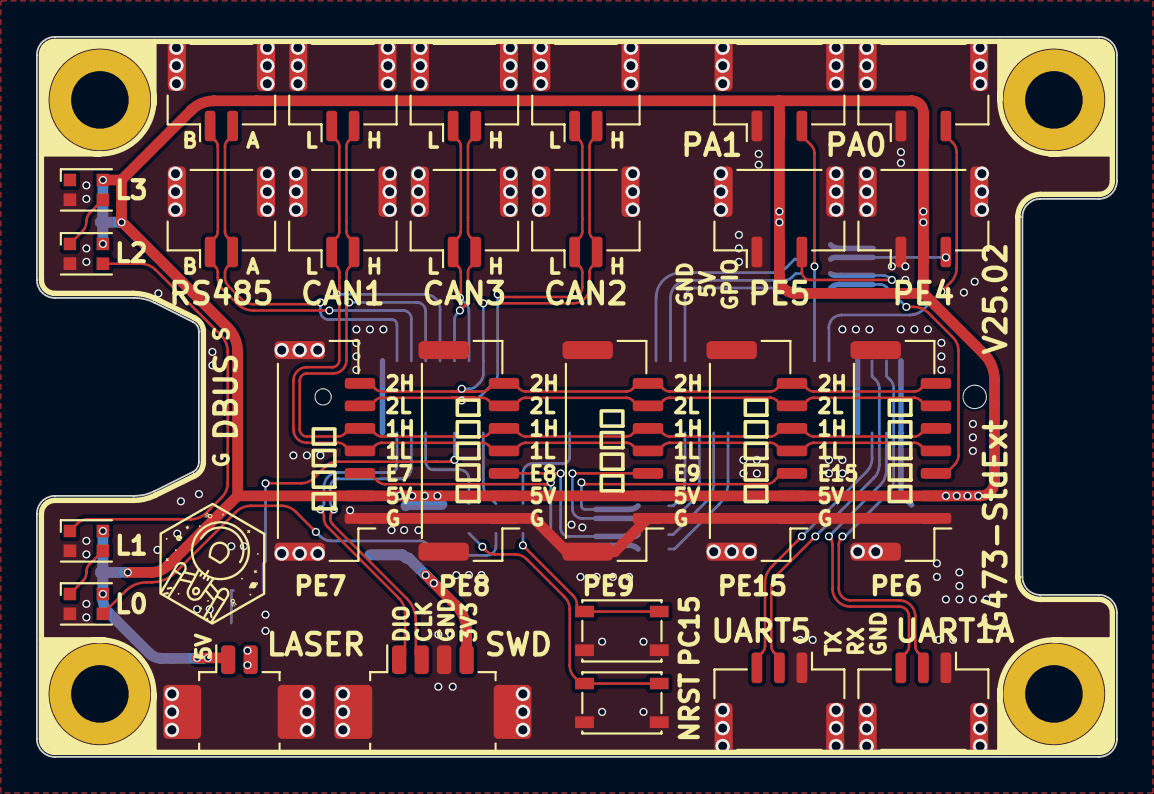
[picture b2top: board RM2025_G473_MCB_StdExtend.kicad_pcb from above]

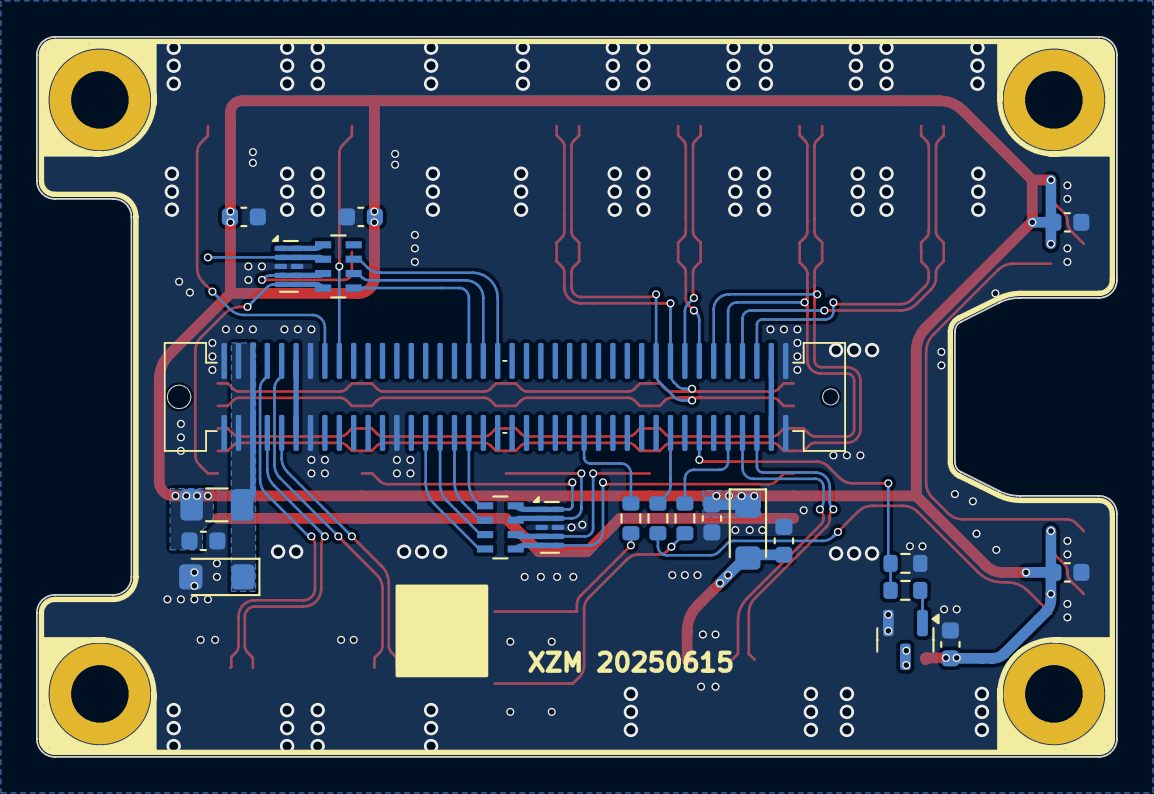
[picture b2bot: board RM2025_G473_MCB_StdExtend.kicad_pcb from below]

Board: 2 copper layers, 60.0 x 40.0 mm, 53 parts (21 on the bottom side), 49 nets.

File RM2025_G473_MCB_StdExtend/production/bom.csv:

Designator,Footprint,Quantity,Value,LCSC Part #
"C1, C2, C3, C4, C5, C6, C78",0603,7,4u7,
C7,0603,1,100n,
"D1, D3, D5",WS2812B-2020,3,WS2812B-2020,
D2,WS2812B-2020,1,RM25:WS2812B-2020,
D4,D_SMF,1,SMFJ5V0A,
D6,D_SMF,1,D_Schottky,
F1,1206,1,1A,
"J1, J14",JST_GH_BM02B-GHS-TBT_1x02-1MP_P1.25mm_Vertical,2,RS-485,
"J10, J11, J2, J3",JST_GH_BM03B-GHS-TBT_1x03-1MP_P1.25mm_Vertical,4,GPIO,
J12,BTB_P0.8mm_2x40pin_M,1,BTB,
"J13, J15, J16, J17, J8, J9",JST_GH_BM02B-GHS-TBT_1x02-1MP_P1.25mm_Vertical,6,CAN,
"J18, J21, J23, J24, J25",JST_GH_BM07B-GHS-TBT_1x07-1MP_P1.25mm_Vertical,5,Conn_01x07_MountingPin,
J19,Molex_PicoBlade_53261-0271_1x02-1MP_P1.25mm_Horizontal,1,LASER,
J28,Molex_PicoBlade_53261-0471_1x04-1MP_P1.25mm_Horizontal,1,SWD,
J6,JST_GH_BM03B-GHS-TBT_1x03-1MP_P1.25mm_Vertical,1,UART1A,
J7,JST_GH_BM03B-GHS-TBT_1x03-1MP_P1.25mm_Vertical,1,UART5,
Q1,SOT-23,1,AO3400A,
"R1, R2, R3, R5",0603,4,120R,
R4,0603,1,10k,
"RN1, RN2",R_Array_Concave_4x0603,2,82R,
SW1,Button_PTS810,1,BTN,
SW2,Button_PTS810,1,NRST,
"U1, U15",USON-10_2.5x1.0mm_P0.5mm_Mod,2,TPD4E02B04DQA,

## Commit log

2025-08-09 工程文件
2025-08-09 ibom和加工文件
2025-08-09 更新readme
